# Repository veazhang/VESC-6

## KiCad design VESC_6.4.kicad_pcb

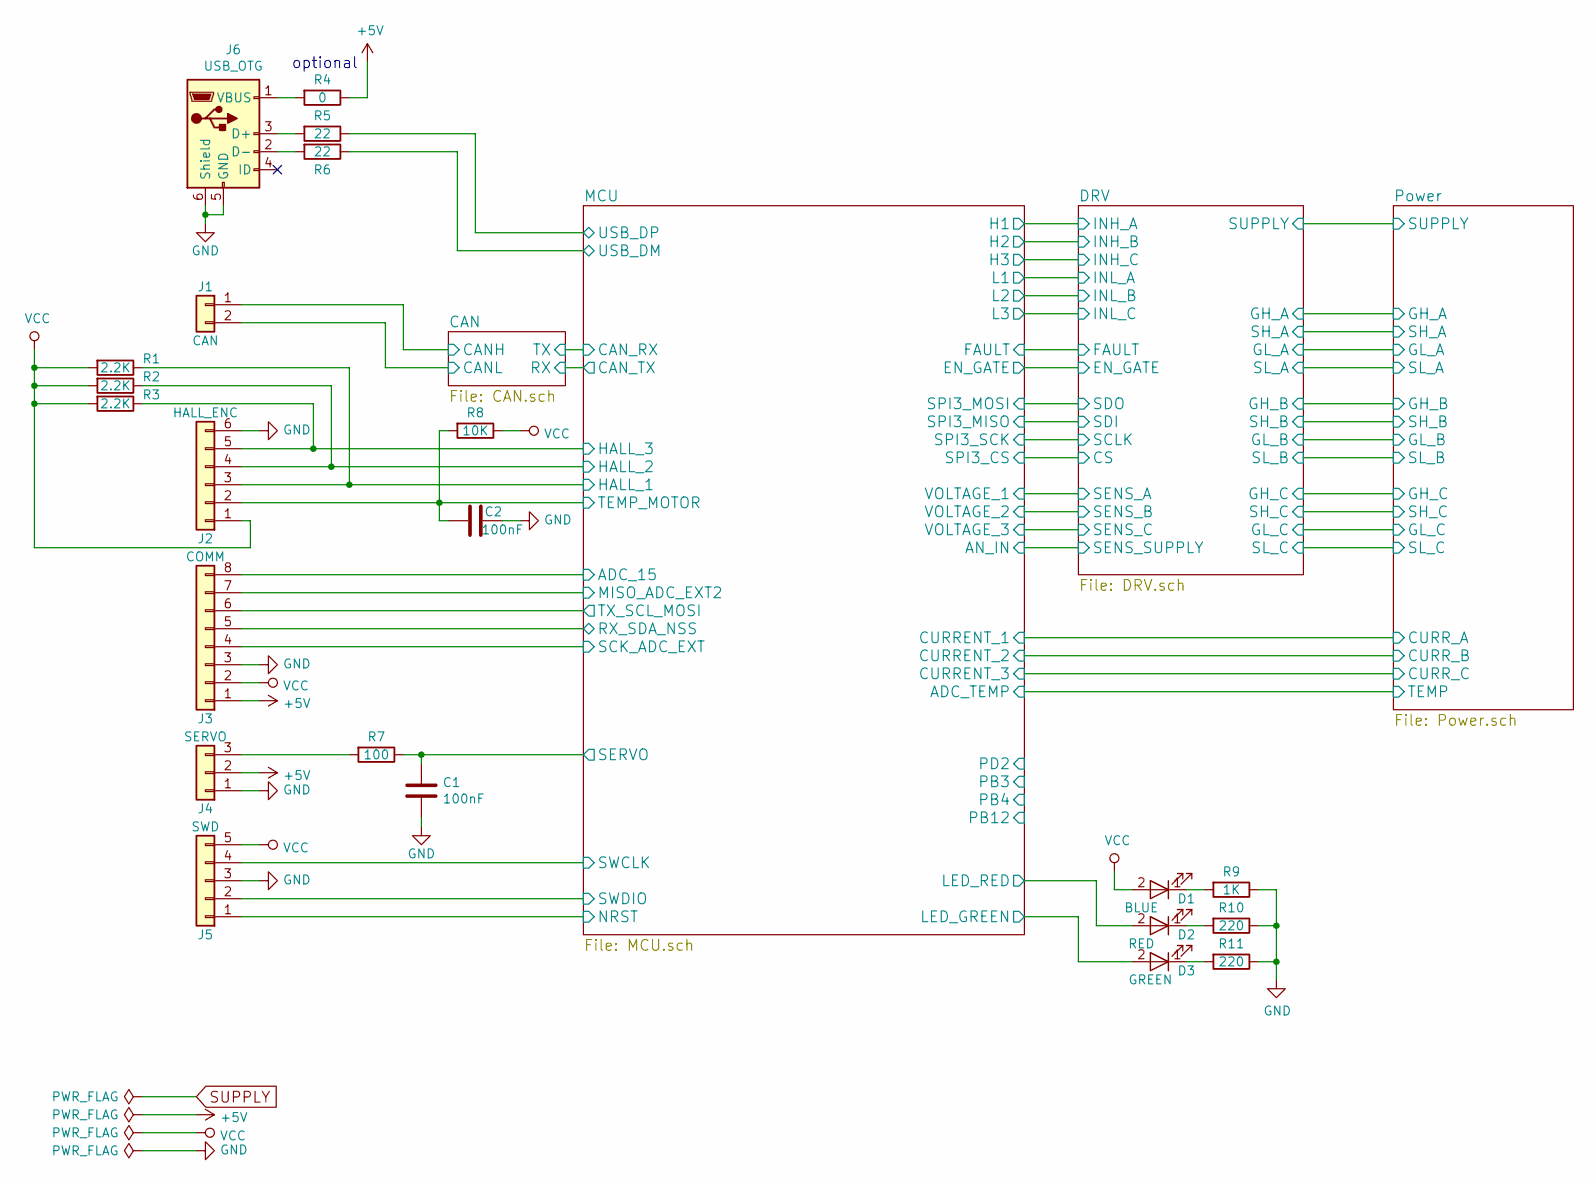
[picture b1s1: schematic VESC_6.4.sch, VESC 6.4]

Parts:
C1, C2: 100nF; C_0603
D1: BLUE; LED_0603
D2: RED; LED_0603
D3: GREEN; LED_0603
J1: CAN; JST_PH_B2B-PH-K_02x2.00mm_Straight
J2: HALL_ENC; JST_PH_B6B-PH-K_06x2.00mm_Straight
J3: COMM; JST_PH_B8B-PH-K_08x2.00mm_Straight
J4: SERVO; JST_PH_B3B-PH-K_03x2.00mm_Straight
J5: SWD; JST_PH_B5B-PH-K_05x2.00mm_Straight
J6: USB_OTG; USB_Micro-B_Molex-105017-0001
R1, R2, R3: 2.2K; R_0603
R4: 0; R_0603
R5, R6: 22; R_0603
R7: 100; R_0603
R8: 10K; R_0603
R9: 1K; R_0603
R10, R11: 220; R_0603

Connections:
+5V: J3.1, J4.2, R4.1; also elsewhere on the board
/CAN/CANH: J1.1; also elsewhere on the board
/CAN/CANL: J1.2; also elsewhere on the board
/MCU/ADC_15: J3.8; also elsewhere on the board
/MCU/HALL_1: J2.3, R1.1; also elsewhere on the board
/MCU/HALL_2: J2.4, R2.1; also elsewhere on the board
/MCU/HALL_3: J2.5, R3.1; also elsewhere on the board
/MCU/LED_GREEN: D3.2 (A); also elsewhere on the board
/MCU/LED_RED: D2.2 (A); also elsewhere on the board
/MCU/MISO_ADC_EXT2: J3.7; also elsewhere on the board
/MCU/NRST: J5.1; also elsewhere on the board
/MCU/RX_SDA_NSS: J3.5; also elsewhere on the board
/MCU/SCK_ADC_EXT: J3.4; also elsewhere on the board
/MCU/SERVO: C1.1, R7.1; also elsewhere on the board
/MCU/SWCLK: J5.4; also elsewhere on the board
/MCU/SWDIO: J5.2; also elsewhere on the board
/MCU/TEMP_MOTOR: C2.1, J2.2, R8.2; also elsewhere on the board
/MCU/TX_SCL_MOSI: J3.6; also elsewhere on the board
/MCU/USB_DM: R6.1; also elsewhere on the board
/MCU/USB_DP: R5.1; also elsewhere on the board
GND: C1.2, C2.2, J2.6, J3.3, J4.1, J5.3, J6.5 (GND), J6.6 (Shield), R9.1, R10.1, R11.1; also elsewhere on the board
unnamed: D1.1 (K), R9.2
unnamed: D2.1 (K), R10.2
unnamed: D3.1 (K), R11.2
unnamed: J4.3, R7.2
unnamed: J6.1 (VBUS), R4.2
unnamed: J6.2 (D-), R6.2
unnamed: J6.3 (D+), R5.2

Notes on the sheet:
optional

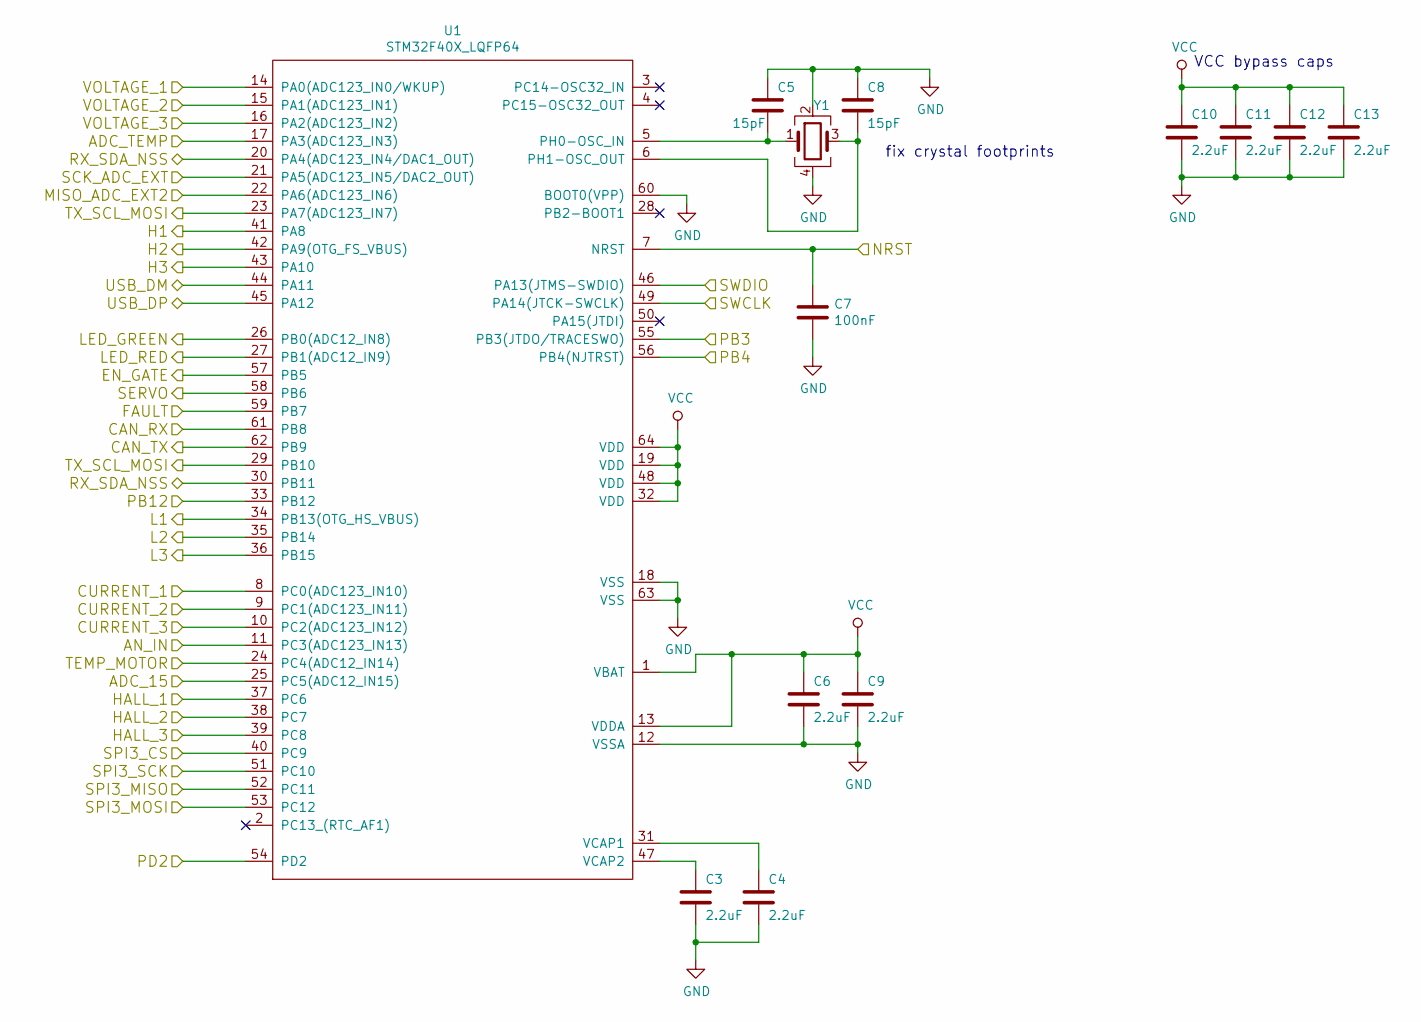
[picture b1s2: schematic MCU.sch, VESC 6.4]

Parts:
C3, C4, C6, C9, C10, C11, C12, C13: 2.2uF; C_0603
C5, C8: 15pF; C_0603
C7: 100nF; C_0603
U1: STM32F40X_LQFP64; LQFP-64_10x10mm_Pitch0.5mm
Y1: Crystal_GND3; Crystal_SMD_Abracon_ABM3B-4pin_5.0x3.2mm

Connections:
/DRV/CS: U1.40 (PC9); also elsewhere on the board
/DRV/EN_GATE: U1.57 (PB5); also elsewhere on the board
/DRV/FAULT: U1.59 (PB7); also elsewhere on the board
/DRV/INL_A: U1.34 (PB13(OTG_HS_VBUS)); also elsewhere on the board
/DRV/INL_B: U1.35 (PB14); also elsewhere on the board
/DRV/INL_C: U1.36 (PB15); also elsewhere on the board
/DRV/SCLK: U1.51 (PC10); also elsewhere on the board
/DRV/SDI: U1.52 (PC11); also elsewhere on the board
/DRV/SDO: U1.53 (PC12); also elsewhere on the board
/DRV/SENS_A: U1.14 (PA0(ADC123_IN0/WKUP)); also elsewhere on the board
/DRV/SENS_B: U1.15 (PA1(ADC123_IN1)); also elsewhere on the board
/DRV/SENS_C: U1.16 (PA2(ADC123_IN2)); also elsewhere on the board
/MCU/ADC_15: U1.25 (PC5(ADC12_IN15)); also elsewhere on the board
/MCU/ADC_TEMP: U1.17 (PA3(ADC123_IN3)); also elsewhere on the board
/MCU/AN_IN: U1.11 (PC3(ADC123_IN13)); also elsewhere on the board
/MCU/CAN_RX: U1.61 (PB8); also elsewhere on the board
/MCU/CAN_TX: U1.62 (PB9); also elsewhere on the board
/MCU/CURRENT_1: U1.8 (PC0(ADC123_IN10)); also elsewhere on the board
/MCU/CURRENT_2: U1.9 (PC1(ADC123_IN11)); also elsewhere on the board
/MCU/CURRENT_3: U1.10 (PC2(ADC123_IN12)); also elsewhere on the board
/MCU/H1: U1.41 (PA8); also elsewhere on the board
/MCU/H2: U1.42 (PA9(OTG_FS_VBUS)); also elsewhere on the board
/MCU/H3: U1.43 (PA10); also elsewhere on the board
/MCU/HALL_1: U1.37 (PC6); also elsewhere on the board
/MCU/HALL_2: U1.38 (PC7); also elsewhere on the board
/MCU/HALL_3: U1.39 (PC8); also elsewhere on the board
/MCU/LED_GREEN: U1.26 (PB0(ADC12_IN8)); also elsewhere on the board
/MCU/LED_RED: U1.27 (PB1(ADC12_IN9)); also elsewhere on the board
/MCU/MISO_ADC_EXT2: U1.22 (PA6(ADC123_IN6)); also elsewhere on the board
/MCU/NRST: C7.1, U1.7 (NRST); also elsewhere on the board
/MCU/PB3: U1.55 (PB3(JTDO/TRACESWO))
/MCU/PB4: U1.56 (PB4(NJTRST))
/MCU/PB12: U1.33 (PB12)
/MCU/PD2: U1.54 (PD2)
/MCU/RX_SDA_NSS: U1.20 (PA4(ADC123_IN4/DAC1_OUT)), U1.30 (PB11); also elsewhere on the board
/MCU/SCK_ADC_EXT: U1.21 (PA5(ADC123_IN5/DAC2_OUT)); also elsewhere on the board
/MCU/SERVO: U1.58 (PB6); also elsewhere on the board
/MCU/SWCLK: U1.49 (PA14(JTCK-SWCLK)); also elsewhere on the board
/MCU/SWDIO: U1.46 (PA13(JTMS-SWDIO)); also elsewhere on the board
/MCU/TEMP_MOTOR: U1.24 (PC4(ADC12_IN14)); also elsewhere on the board
/MCU/TX_SCL_MOSI: U1.23 (PA7(ADC123_IN7)), U1.29 (PB10); also elsewhere on the board
/MCU/USB_DM: U1.44 (PA11); also elsewhere on the board
/MCU/USB_DP: U1.45 (PA12); also elsewhere on the board
GND: C3.2, C4.2, C5.1, C6.2, C7.2, C8.1, C9.2, C10.2, C11.2, C12.2, C13.2, U1.12 (VSSA), U1.18 (VSS), U1.60 (BOOT0(VPP)), U1.63 (VSS), Y1.2, Y1.4; also elsewhere on the board
unnamed: C3.1, U1.47 (VCAP2)
unnamed: C4.1, U1.31 (VCAP1)
unnamed: C5.2, U1.5 (PH0-OSC_IN), Y1.1
unnamed: C8.2, U1.6 (PH1-OSC_OUT), Y1.3

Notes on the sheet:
VCC bypass caps
fix crystal footprints

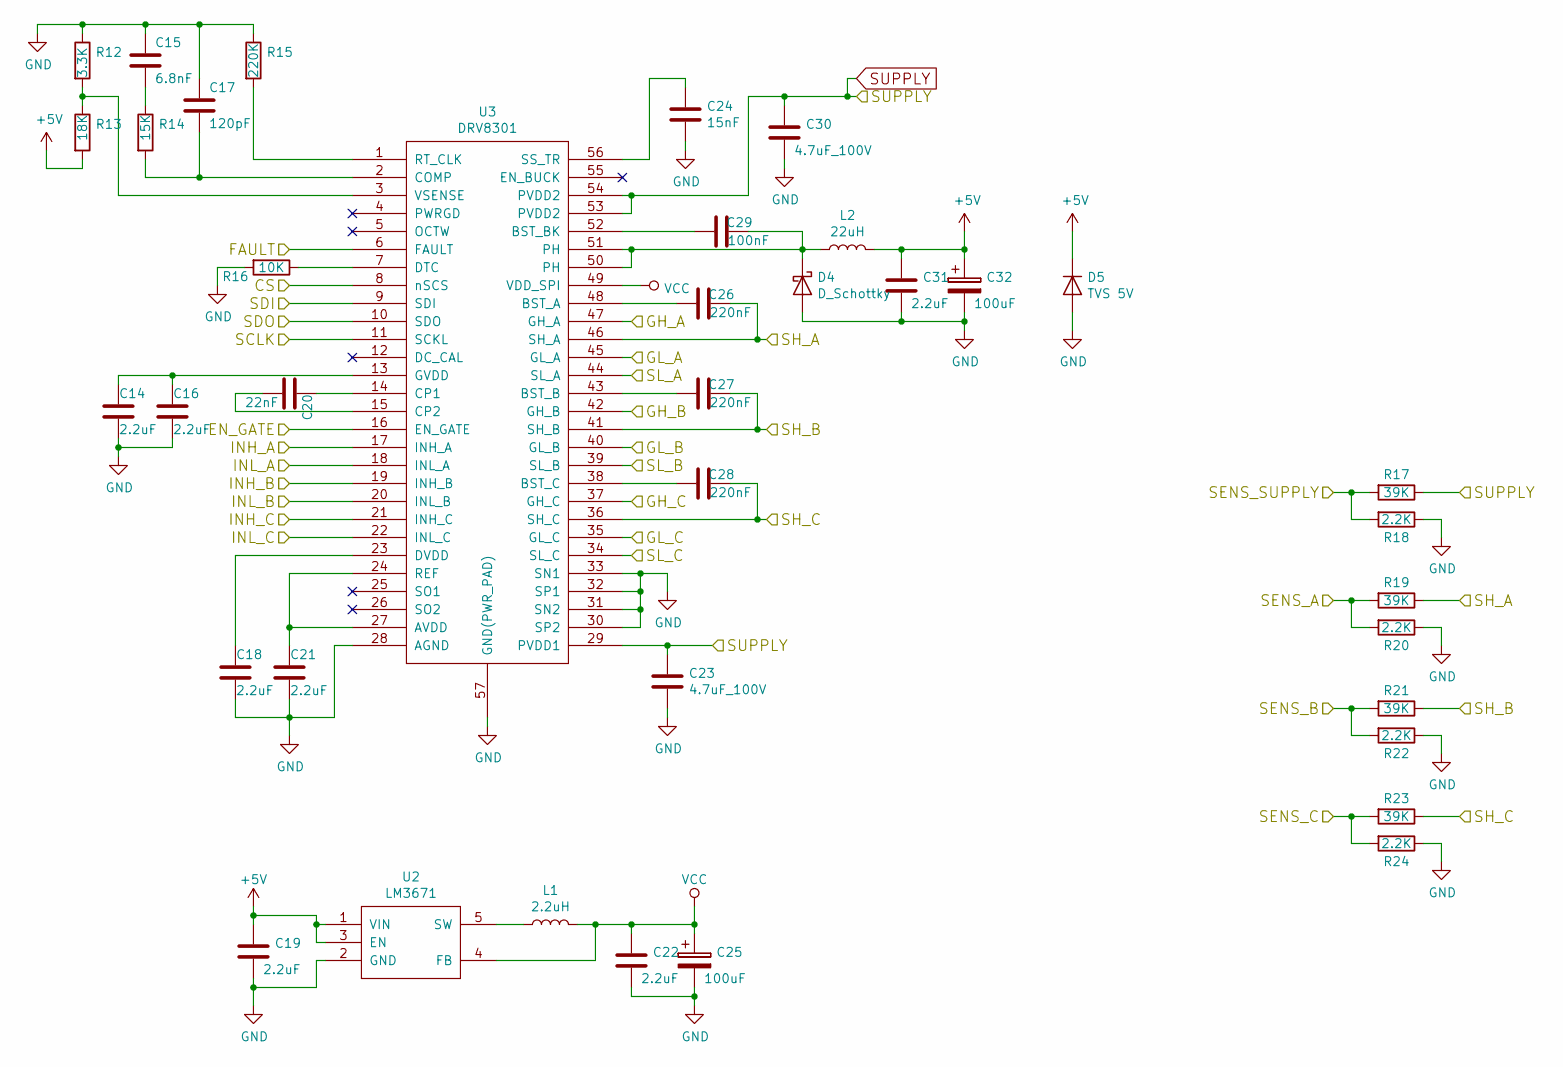
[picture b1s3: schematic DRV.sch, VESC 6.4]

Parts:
C14, C16, C18, C19, C21, C22, C31: 2.2uF; C_0603
C15: 6.8nF; C_0603
C17: 120pF; C_0603
C20: 22nF; C_0603
C23, C30: 4.7uF_100V; C_1210
C24: 15nF; C_0603
C25, C32: 100uF; C_1210
C26, C27, C28: 220nF; C_0603
C29: 100nF; C_0603
D4: D_Schottky; D_SOD-123
D5: TVS 5V; D_SMA
L1: 2.2uH; L_0805
L2: 22uH; SRN8040
R12: 3.3K; R_0603
R13: 18K; R_0603
R14: 15K; R_0603
R15: 220K; R_0603
R16: 10K; R_0603
R17, R19, R21, R23: 39K; R_0603
R18, R20, R22, R24: 2.2K; R_0603
U2: LM3671; SOT-23-5
U3: DRV8301; 56-HTSSOP

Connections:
+5V: C19.1, C31.1, C32.1, D5.1 (K), L2.2, R13.2, U2.1 (VIN), U2.3 (EN); also elsewhere on the board
/DRV/CS: U3.8 (nSCS); also elsewhere on the board
/DRV/EN_GATE: U3.16 (EN_GATE); also elsewhere on the board
/DRV/FAULT: U3.6 (FAULT); also elsewhere on the board
/DRV/GH_A: U3.47 (GH_A); also elsewhere on the board
/DRV/GH_B: U3.42 (GH_B); also elsewhere on the board
/DRV/GH_C: U3.37 (GH_C); also elsewhere on the board
/DRV/GL_A: U3.45 (GL_A); also elsewhere on the board
/DRV/GL_B: U3.40 (GL_B); also elsewhere on the board
/DRV/GL_C: U3.35 (GL_C); also elsewhere on the board
/DRV/INL_A: U3.18 (INL_A); also elsewhere on the board
/DRV/INL_B: U3.20 (INL_B); also elsewhere on the board
/DRV/INL_C: U3.22 (INL_C); also elsewhere on the board
/DRV/SCLK: U3.11 (SCKL); also elsewhere on the board
/DRV/SDI: U3.9 (SDI); also elsewhere on the board
/DRV/SDO: U3.10 (SDO); also elsewhere on the board
/DRV/SENS_A: R19.2, R20.2; also elsewhere on the board
/DRV/SENS_B: R21.2, R22.2; also elsewhere on the board
/DRV/SENS_C: R23.2, R24.2; also elsewhere on the board
/DRV/SH_A: C26.1, R19.1, U3.46 (SH_A); also elsewhere on the board
/DRV/SH_B: C27.1, R21.1, U3.41 (SH_B); also elsewhere on the board
/DRV/SH_C: C28.1, R23.1, U3.36 (SH_C); also elsewhere on the board
/MCU/AN_IN: R17.2, R18.2; also elsewhere on the board
/MCU/H1: U3.17 (INH_A); also elsewhere on the board
/MCU/H2: U3.19 (INH_B); also elsewhere on the board
/MCU/H3: U3.21 (INH_C); also elsewhere on the board
GND: C14.2, C15.1, C16.2, C17.1, C18.2, C19.2, C21.2, C22.2, C23.2, C24.2, C25.2, C30.2, C31.2, C32.2, D4.2 (A), D5.2 (A), R12.1, R15.1, R16.2, R18.1, R20.1, R22.1, R24.1, U2.2 (GND), U3.28 (AGND), U3.30 (SP2), U3.31 (SN2), U3.32 (SP1), U3.33 (SN1), U3.34 (SL_C), U3.39 (SL_B), U3.44 (SL_A), U3.57 (GND(PWR_PAD)); also elsewhere on the board
unnamed: C14.1, C16.1, U3.13 (GVDD)
unnamed: C15.2, R14.1
unnamed: C17.2, R14.2, U3.2 (COMP)
unnamed: C18.1, U3.23 (DVDD)
unnamed: C20.1, U3.14 (CP1)
unnamed: C20.2, U3.15 (CP2)
unnamed: C21.1, U3.24 (REF), U3.27 (AVDD)
unnamed: C24.1, U3.56 (SS_TR)
unnamed: C26.2, U3.48 (BST_A)
unnamed: C27.2, U3.43 (BST_B)
unnamed: C28.2, U3.38 (BST_C)
unnamed: C29.1, D4.1 (K), L2.1, U3.50 (PH), U3.51 (PH)
unnamed: C29.2, U3.52 (BST_BK)
unnamed: L1.1, U2.5 (SW)
unnamed: R12.2, R13.1, U3.3 (VSENSE)
unnamed: R15.2, U3.1 (RT_CLK)
unnamed: R16.1, U3.7 (DTC)
SUPPLY: C23.1, C30.1, R17.1, U3.29 (PVDD1), U3.53 (PVDD2), U3.54 (PVDD2); also elsewhere on the board

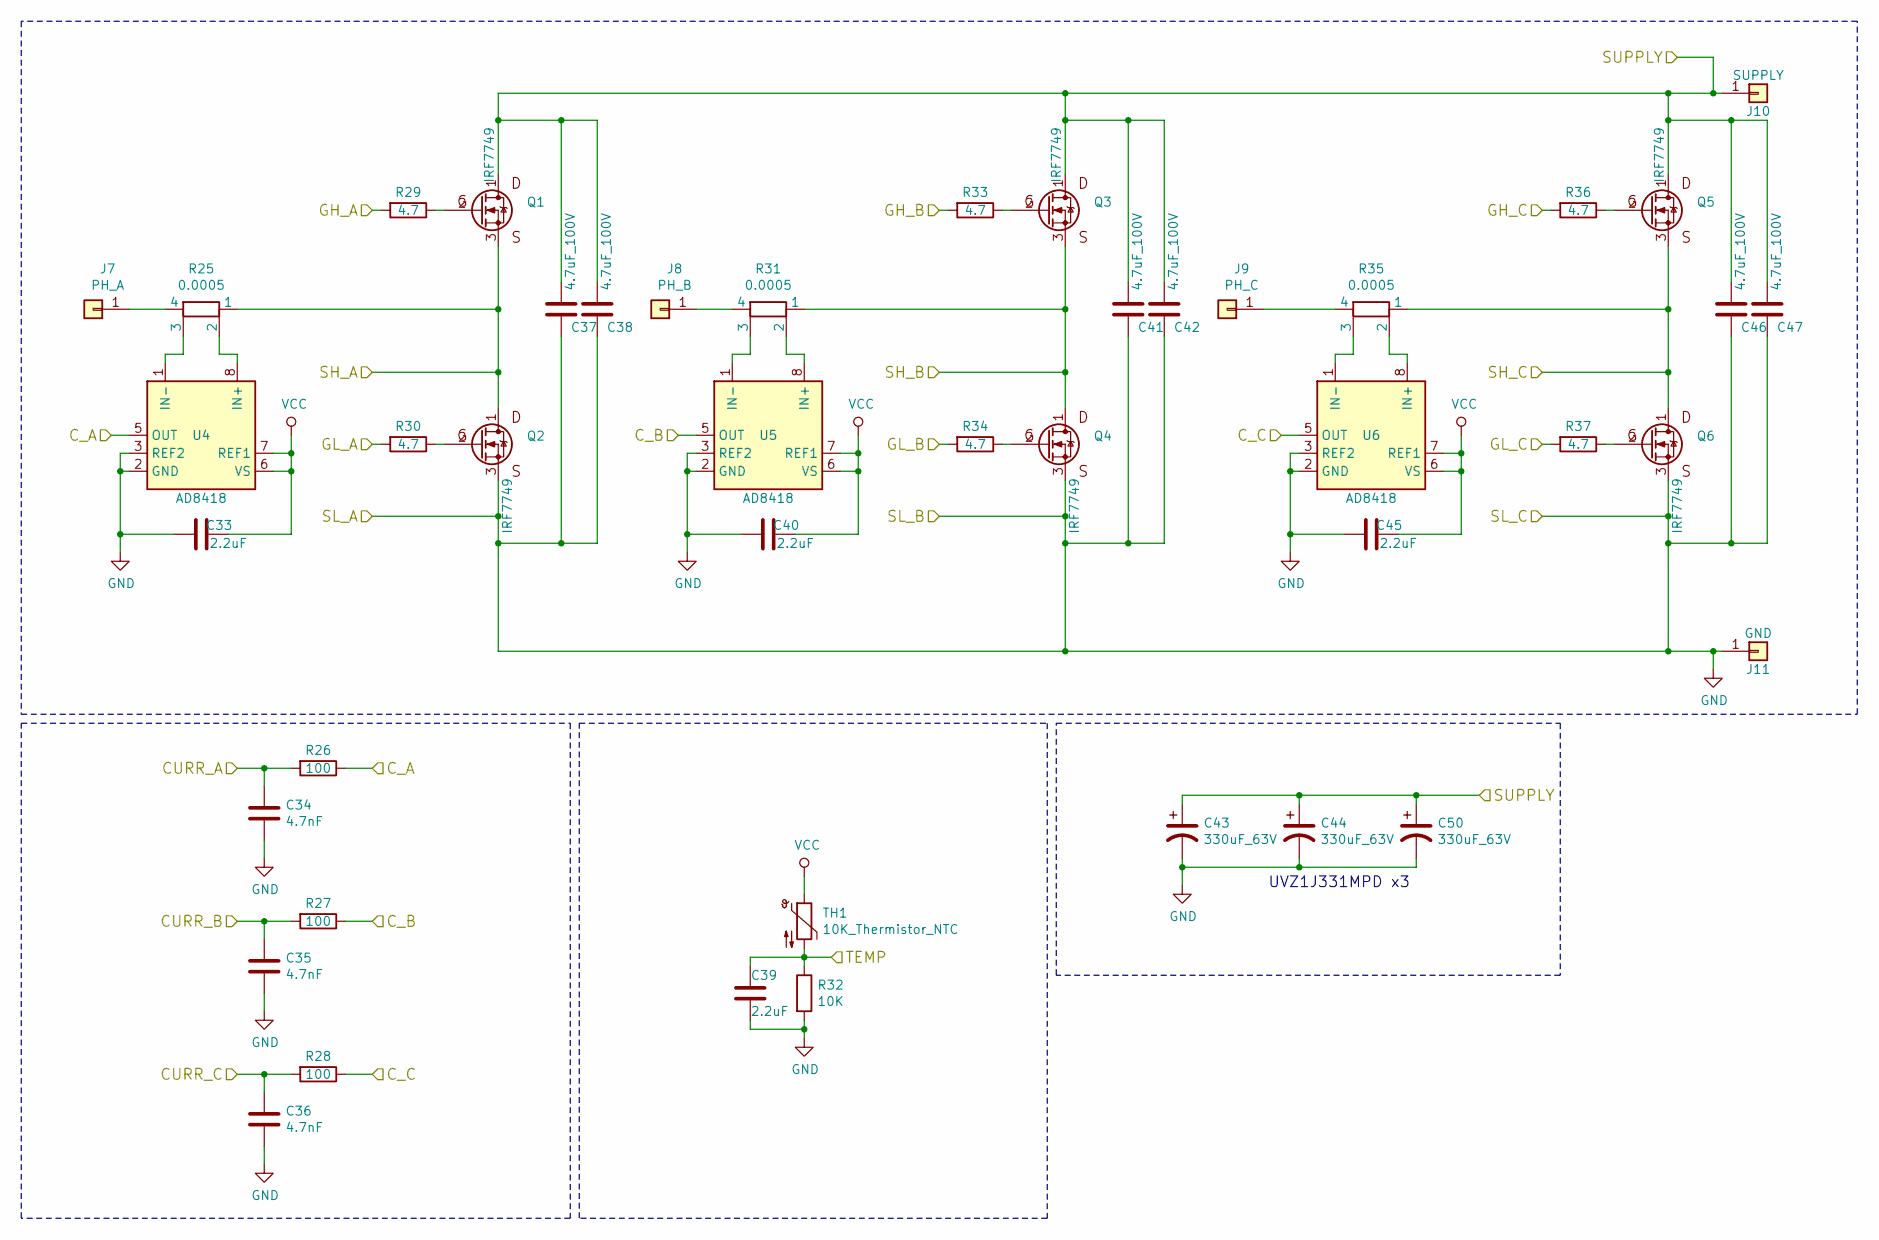
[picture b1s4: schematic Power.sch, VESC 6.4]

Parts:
C33, C39, C40, C45: 2.2uF; C_0603
C34, C35, C36: 4.7nF; C_0603
C37, C38, C41, C42, C46, C47: 4.7uF_100V; C_1210
C43, C44, C50: 330uF_63V; CP_Radial_D10.0mm_P5.00mm
J7: PH_A; SolderWirePad_single_SMD_5x5mm
J8: PH_B; SolderWirePad_single_SMD_5x5mm
J9: PH_C; SolderWirePad_single_SMD_5x5mm
J10: SUPPLY; SolderWirePad_single_SMD_6.5x6.5mm
J11: GND; SolderWirePad_single_SMD_6.5x6.5mm
Q1, Q2, Q3, Q4, Q5, Q6: IRF7749; DirectFET_L8
R25, R31, R35: 0.0005; 3920
R26, R27, R28: 100; R_0603
R29, R30, R33, R34, R36, R37: 4.7; R_0603
R32: 10K; R_0603
TH1: 10K_Thermistor_NTC; R_0603
U4, U5, U6: AD8418; SOIC-8_3.9x4.9mm_Pitch1.27mm

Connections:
/DRV/GH_A: R29.2; also elsewhere on the board
/DRV/GH_B: R33.2; also elsewhere on the board
/DRV/GH_C: R36.2; also elsewhere on the board
/DRV/GL_A: R30.2; also elsewhere on the board
/DRV/GL_B: R34.2; also elsewhere on the board
/DRV/GL_C: R37.2; also elsewhere on the board
/DRV/SH_A: Q1.3 (S), Q2.1 (D), R25.1; also elsewhere on the board
/DRV/SH_B: Q3.3 (S), Q4.1 (D), R31.1; also elsewhere on the board
/DRV/SH_C: Q5.3 (S), Q6.1 (D), R35.1; also elsewhere on the board
/MCU/ADC_TEMP: C39.1, R32.1, TH1.2; also elsewhere on the board
/MCU/CURRENT_1: C34.1, R26.2; also elsewhere on the board
/MCU/CURRENT_2: C35.1, R27.2; also elsewhere on the board
/MCU/CURRENT_3: C36.1, R28.2; also elsewhere on the board
/Power/C_A: R26.1, U4.5 (OUT)
/Power/C_B: R27.1, U5.5 (OUT)
/Power/C_C: R28.1, U6.5 (OUT)
GND: C33.2, C34.2, C35.2, C36.2, C37.2, C38.2, C39.2, C40.2, C41.2, C42.2, C43.2, C44.2, C45.2, C46.2, C47.2, C50.2, J11.1, Q2.3 (S), Q4.3 (S), Q6.3 (S), R32.2, U4.2 (GND), U4.3 (REF2), U5.2 (GND), U5.3 (REF2), U6.2 (GND), U6.3 (REF2); also elsewhere on the board
unnamed: J7.1, R25.4
unnamed: J8.1, R31.4
unnamed: J9.1, R35.4
unnamed: Q1.2 (G), R29.1
unnamed: Q2.2 (G), R30.1
unnamed: Q3.2 (G), R33.1
unnamed: Q4.2 (G), R34.1
unnamed: Q5.2 (G), R36.1
unnamed: Q6.2 (G), R37.1
unnamed: R25.2, U4.8 (IN+)
unnamed: R25.3, U4.1 (IN-)
unnamed: R31.2, U5.8 (IN+)
unnamed: R31.3, U5.1 (IN-)
unnamed: R35.2, U6.8 (IN+)
unnamed: R35.3, U6.1 (IN-)
SUPPLY: C37.1, C38.1, C41.1, C42.1, C43.1, C44.1, C46.1, C47.1, C50.1, J10.1, Q1.1 (D), Q3.1 (D), Q5.1 (D); also elsewhere on the board

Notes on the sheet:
UVZ1J331MPD x3

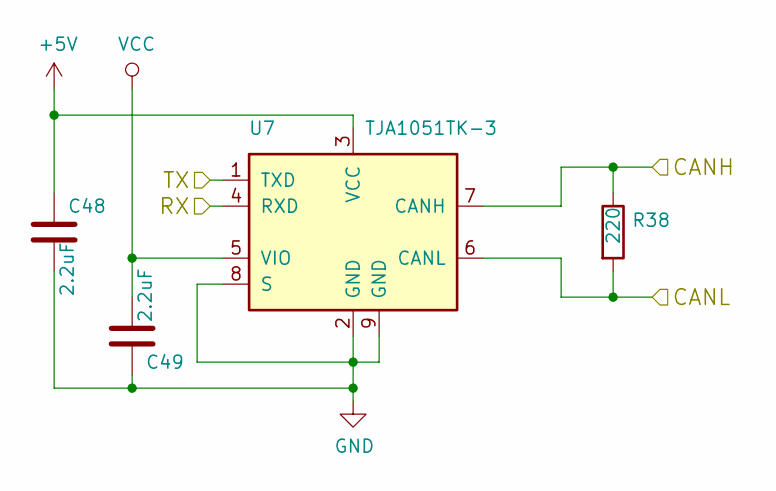
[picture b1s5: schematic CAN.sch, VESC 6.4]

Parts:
C48, C49: 2.2uF; C_0603
R38: 220; R_0603
U7: TJA1051TK-3; Texas_S-PVSON-N8

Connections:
+5V: C48.1, U7.3 (VCC); also elsewhere on the board
/CAN/CANH: R38.1, U7.7 (CANH); also elsewhere on the board
/CAN/CANL: R38.2, U7.6 (CANL); also elsewhere on the board
/MCU/CAN_RX: U7.1 (TXD); also elsewhere on the board
/MCU/CAN_TX: U7.4 (RXD); also elsewhere on the board
GND: C48.2, C49.2, U7.2 (GND), U7.8 (S), U7.9 (GND); also elsewhere on the board

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
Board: 4 copper layers, 122 parts (19 on the bottom side), 101 nets, no tracks yet.

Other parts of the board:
SW1: SENSOR_VOLTAGE; JS102011JCQN

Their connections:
+5V: SW1.3; also elsewhere on the board

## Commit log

2018-02-17 initial commit
    schematic completed
    PCB in progress
2018-02-25 minor PCB work
2018-02-26 lots of PCB work
2018-02-27 power electronics PCB work
2018-02-27 Continued Work on the PCB
2018-02-28 power electronics almost done
2018-03-02 its a dark and scary night in kicad land
2018-03-02 the PCB trace gremlins were creeping around
2018-03-02 the save button tried its hardest to stay safe from the gremlins
2018-03-02 sometimes the gremlins would delete all of the save buttons work!
2018-03-02 dun dun dun
2018-03-02 something ate the power electronics ground plane!
2018-03-04 Rev1a done
2018-03-05 changed the USB port around added CAD stuff
2018-03-06 added logo and rev number
2018-03-28 moved a diode slightly, fixed a DRC issue
2018-03-29 trying out a new PCB shape, trimmed away NRF and MPU
2018-04-08 rounded the PCB corners
2018-04-09 removed 5v/3v3 sensor switch
2018-04-12 removed sensor switch
2018-04-12 fixed vias, updated PCB per schematic
2018-04-19 updated gerbers
2018-04-19 moved files around
2018-04-19 silkscreen fixes on PCB
2018-05-04 removed HALL switch, added bulk capacitor, updated sheet's datestamp
2018-05-04 PCB work, arranging footprints
2018-05-12 bunch more part placement
